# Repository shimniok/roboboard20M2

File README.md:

# roboboard20M2
Robot Controller board for PICAXE-20M2

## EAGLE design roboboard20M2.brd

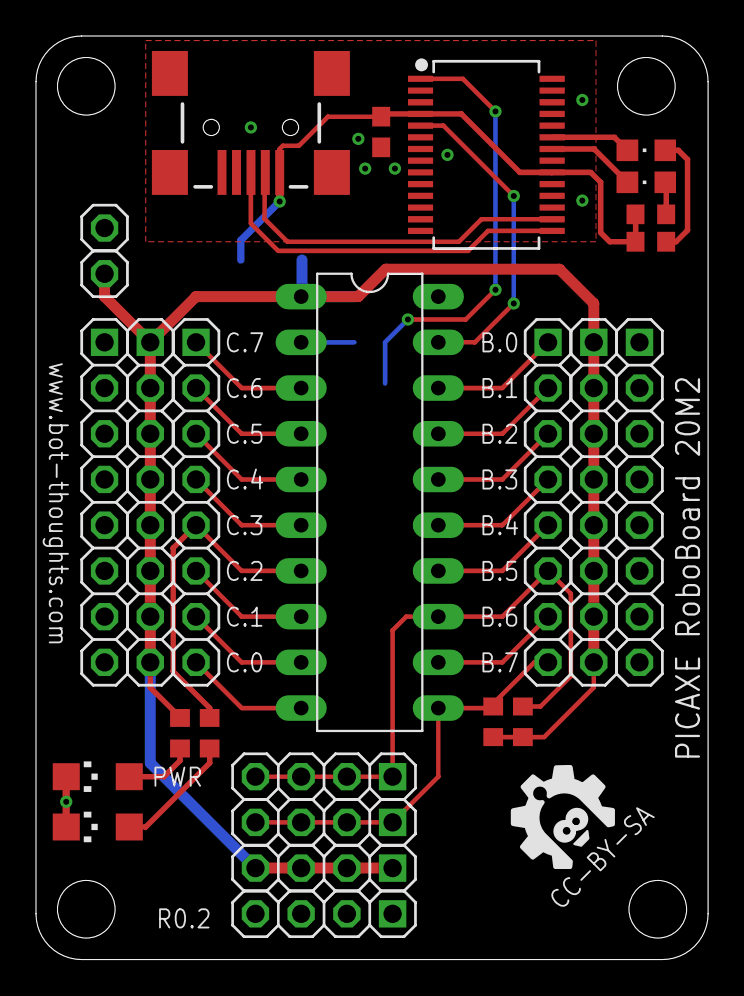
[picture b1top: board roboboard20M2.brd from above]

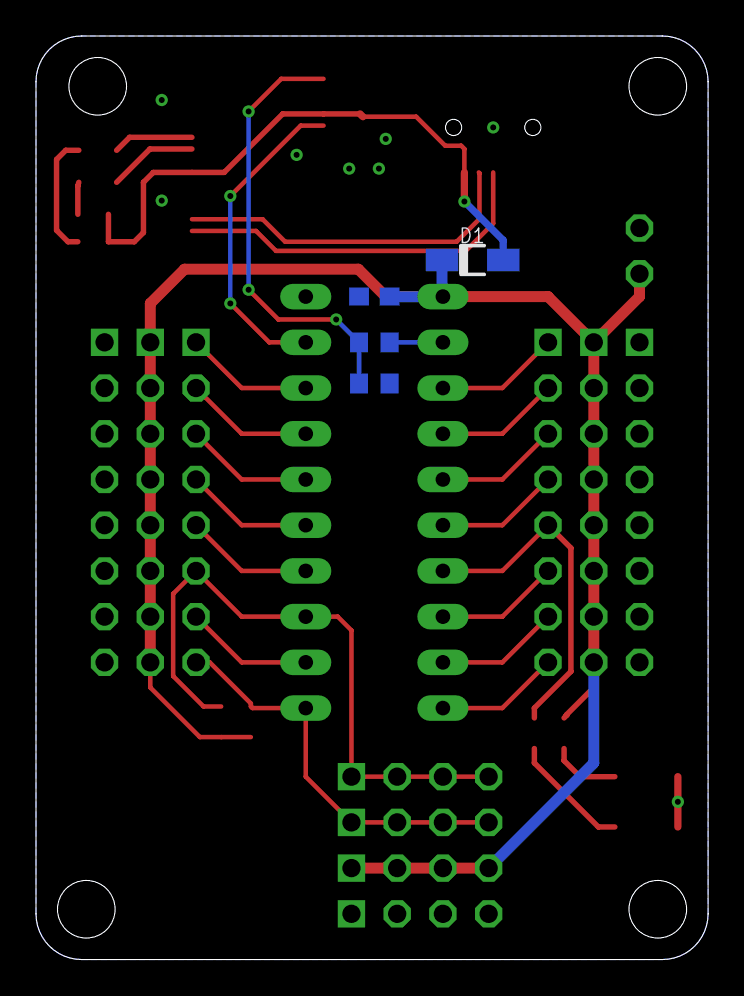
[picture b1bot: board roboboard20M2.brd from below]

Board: 2 copper layers, 37.3 x 51.3 mm, 31 parts (4 on the bottom side), 30 nets.

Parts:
C1, C2: 104; C0603
D1: DIODE; SOD123FL
JP2: 5V; 1X01-S
JP3: SCL; 1X04-S
JP4: SDA; 1X04-S
JP5: VDD; 1X04-S
JP6: GND; 1X04-S
JP7: C; 1X08-S
JP8, JP17: VDD; 1X08-S
JP9, JP16: GND; 1X08-S
JP10: USB-MINIB
JP14: GND; 1X01-S
JP15: B; 1X08-S
LED1: TX; CHIPLED_0805
LED2: C.3; CHIPLED_1206
LED3: RX; CHIPLED_0805
PWR: CHIPLED_1206
R1: 22K; R0603
R2, R3, R7: 10K; R0603
R4, R5, R6, R8: 330; R0603
U1: PICAXE-20M2; DIL20
U4: FT232RL; SSOP28DB
U$10: BTLOGO-LOGO-MD; BTLOGOM

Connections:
B.0: JP15.1, U1.18
B.1: JP15.2, U1.17
B.2: JP15.3, U1.16
B.3: JP15.4, U1.15
B.4: JP15.5, U1.14
B.5: JP4.1, JP4.2, JP4.3, JP4.4, JP15.6, R3.1, U1.13
B.6: JP15.7, U1.12
B.7: JP3.1, JP3.2, JP3.3, JP3.4, JP15.8, R2.1, U1.11
C.0: JP7.8, U1.10
C.1: JP7.7, U1.9
C.2: JP7.6, U1.8
C.3: JP7.5, R8.1, U1.7
C.4: JP7.4, U1.6
C.5: JP7.3, U1.5
C.6: JP7.2, U1.4
C.7: JP7.1, U1.3
GND: C1.2, C2.2, JP6.1, JP6.2, JP6.3, JP6.4, JP9.1, JP9.2, JP9.3, JP9.4, JP9.5, JP9.6, JP9.7, JP9.8, JP10.GND, JP10.MTN1, JP10.MTN2, JP10.MTN3, JP10.MTN4, JP14.1, JP16.1, JP16.2, JP16.3, JP16.4, JP16.5, JP16.6, JP16.7, JP16.8, LED2.C, PWR.C, R7.2, U1.20, U4.7, U4.18, U4.21, U4.25, U4.26
unnamed: LED2.A, R8.2
unnamed: PWR.A, R6.2
unnamed: LED1.C, U4.23
unnamed: LED1.A, R4.2
unnamed: LED3.A, R5.2
unnamed: JP10.D-, U4.16
unnamed: JP10.D+, U4.15
unnamed: LED3.C, U4.22
RX: R1.2, U1.2
SERIN: R1.1, R7.1, U4.1
SEROUT: U1.19, U4.5
VBUS: C2.1, D1.A, JP10.VBUS, R4.1, R5.1, U4.4, U4.20
VDD: C1.1, D1.C, JP2.1, JP5.1, JP5.2, JP5.3, JP5.4, JP8.1, JP8.2, JP8.3, JP8.4, JP8.5, JP8.6, JP8.7, JP8.8, JP17.1, JP17.2, JP17.3, JP17.4, JP17.5, JP17.6, JP17.7, JP17.8, R2.2, R3.2, R6.1, U1.1

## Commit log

2016-12-27 fixed pin labeling (C, B), fixed SDA/SCL connection, tweaked layout of: logo, underside passives. Rerouted most traces and put pin traces on top; altered 10k pullup location.
2016-12-27 add gerbers, zip
2016-12-27 Updated gerbers, zip

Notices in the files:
roboboard20M2.brd:
CC-BY-SA
parts and their libraries:
SparkFun-DigitalIC: Licensing: Creative Commons ShareAlike 4.0 International - https://creativecommons.org/licenses/by-sa/4.0
